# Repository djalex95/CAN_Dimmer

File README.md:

# CAN LED Dimmer

Vierkanaliger LED-Dimmer mit CAN-Bus und Bluetooth LE, entwickelt in KiCad 10.

## Eckdaten

- 4 LED-KanÃ¤le mit je etwa 5 A, PWM 1 kHz (strombegrenzte LED-Streifen als Last angenommen)
- Versorgung 12 V nominal, 24 V optional; zwei Eingangszweige mit je 10-A-Sicherung und TVS-Schutz
- Steuerung: STM32G0B1CEU6 (UFQFPN48, 7 x 7 mm, 512 KB Flash) mit externem 8-MHz-Quarz
- Kommunikation: CAN (TLT9251VLE, externe Terminierung) und Bluetooth LE (WÃ¼rth Proteus-IV 2621011024000)
- High-Side-Schalter BTS70202 (je zwei KanÃ¤le) mit Stromdiagnose, P-Kanal-MOSFETs fÃ¼r die Lastzweige
- Spannungsversorgung: LM5166X (5 V) und NCP730 (3,3 V)
- 4 TastereingÃ¤nge (J5), EEPROM M24C04, Programmierung Ã¼ber Tag-Connect TC2030 (J1, J2)
- Platine 100 Ã— 75 mm, 4 Lagen, 1,6 mm, nur Oberseite bestÃ¼ckt, vier Montagebohrungen Ã˜ 3,2 mm

## Aufbau des Projekts

| Datei / Ordner | Inhalt |
|---|---|
| `CAN LED Dimmer.kicad_pro` | Projektdatei, hier Ã¶ffnen |
| `CAN LED Dimmer.kicad_sch` | Schaltplan-Ãœbersicht (hierarchisch) |
| `CAN_LED_Dimmer_MCU.kicad_sch` | Blatt MCU, Bluetooth, CAN |
| `CAN_LED_Dimmer_2.kicad_sch` | Blatt Spannungsversorgung |
| `CAN_LED_Dimmer_3.kicad_sch` | Blatt LED-AusgÃ¤nge |
| `CAN LED Dimmer.kicad_pcb` | Platinenlayout |
| `CAN LED Dimmer-eagle-import.kicad_sym` | Symbolbibliothek (aus Eagle/Fusion importiert) |
| `CAN_LED_Dimmer-layout.pretty` | angepasste Footprint-Varianten fÃ¼r dieses Layout |
| `3dmodels/` | 3D-Modelle, Herkunft siehe `3dmodels/README-3D.md` |

Alle Bibliotheken und 3D-Modelle liegen im Projekt und sind Ã¼ber `${KIPRJMOD}` eingebunden. Nach dem Klonen reicht eine KiCad-10-Installation, es mÃ¼ssen keine Bibliothekspfade angepasst werden.

## Ã–ffnen

1. Repository klonen oder als ZIP herunterladen.
2. In KiCad 10 die Datei `CAN LED Dimmer.kicad_pro` Ã¶ffnen.

## Stand

Arbeitsstand, noch keine Fertigungsfreigabe:

- Layout vollstÃ¤ndig geroutet, DRC zuletzt ohne Fehler und offene Verbindungen; bekannte Bibliotheks- und Silkscreen-Warnungen sind noch offen.
- ERC hat noch offene Meldungen, vor allem durch importierte Pin-Typen.
- Strombelastbarkeit, Thermik bei viermal 5 A und Schaltflanken sind am Prototyp zu prÃ¼fen.
- Lagenaufbau und Kupferdicke sind mit dem Hersteller festzulegen.
- Eingangsschutz fÃ¼r 24 V und Transienten ist bewusst zurÃ¼ckgestellt.

Historische Reviews, Zwischenstände und unbenutzte Importdateien wurden separat außerhalb des Projektordners archiviert. Die aktive Footprint-Bibliothek ist `CAN_LED_Dimmer-layout.pretty`.

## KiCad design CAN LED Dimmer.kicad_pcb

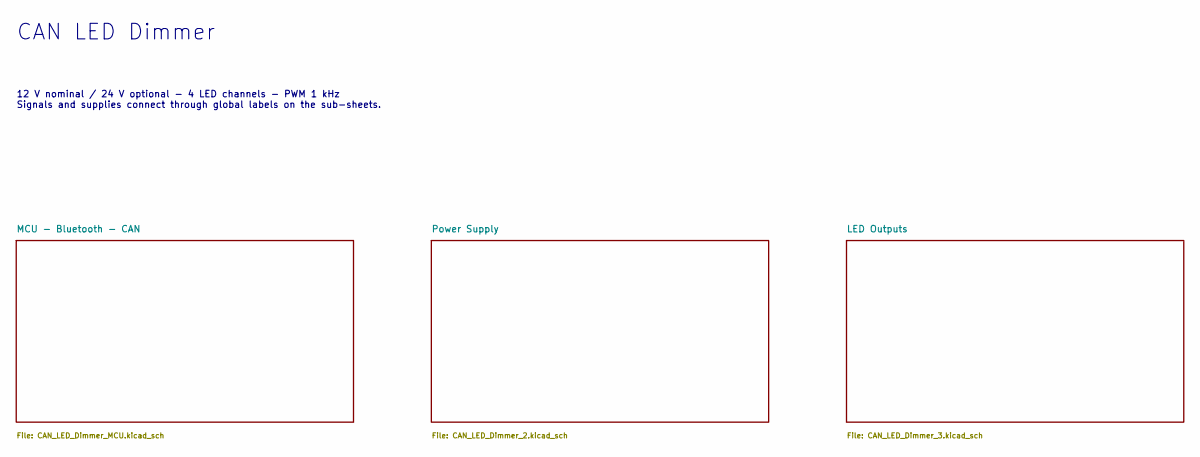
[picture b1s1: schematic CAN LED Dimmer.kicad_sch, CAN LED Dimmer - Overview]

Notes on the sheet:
CAN LED Dimmer
12 V nominal / 24 V optional - 4 LED channels - PWM 1 kHz Signals and supplies connect through global labels on the sub-sheets.

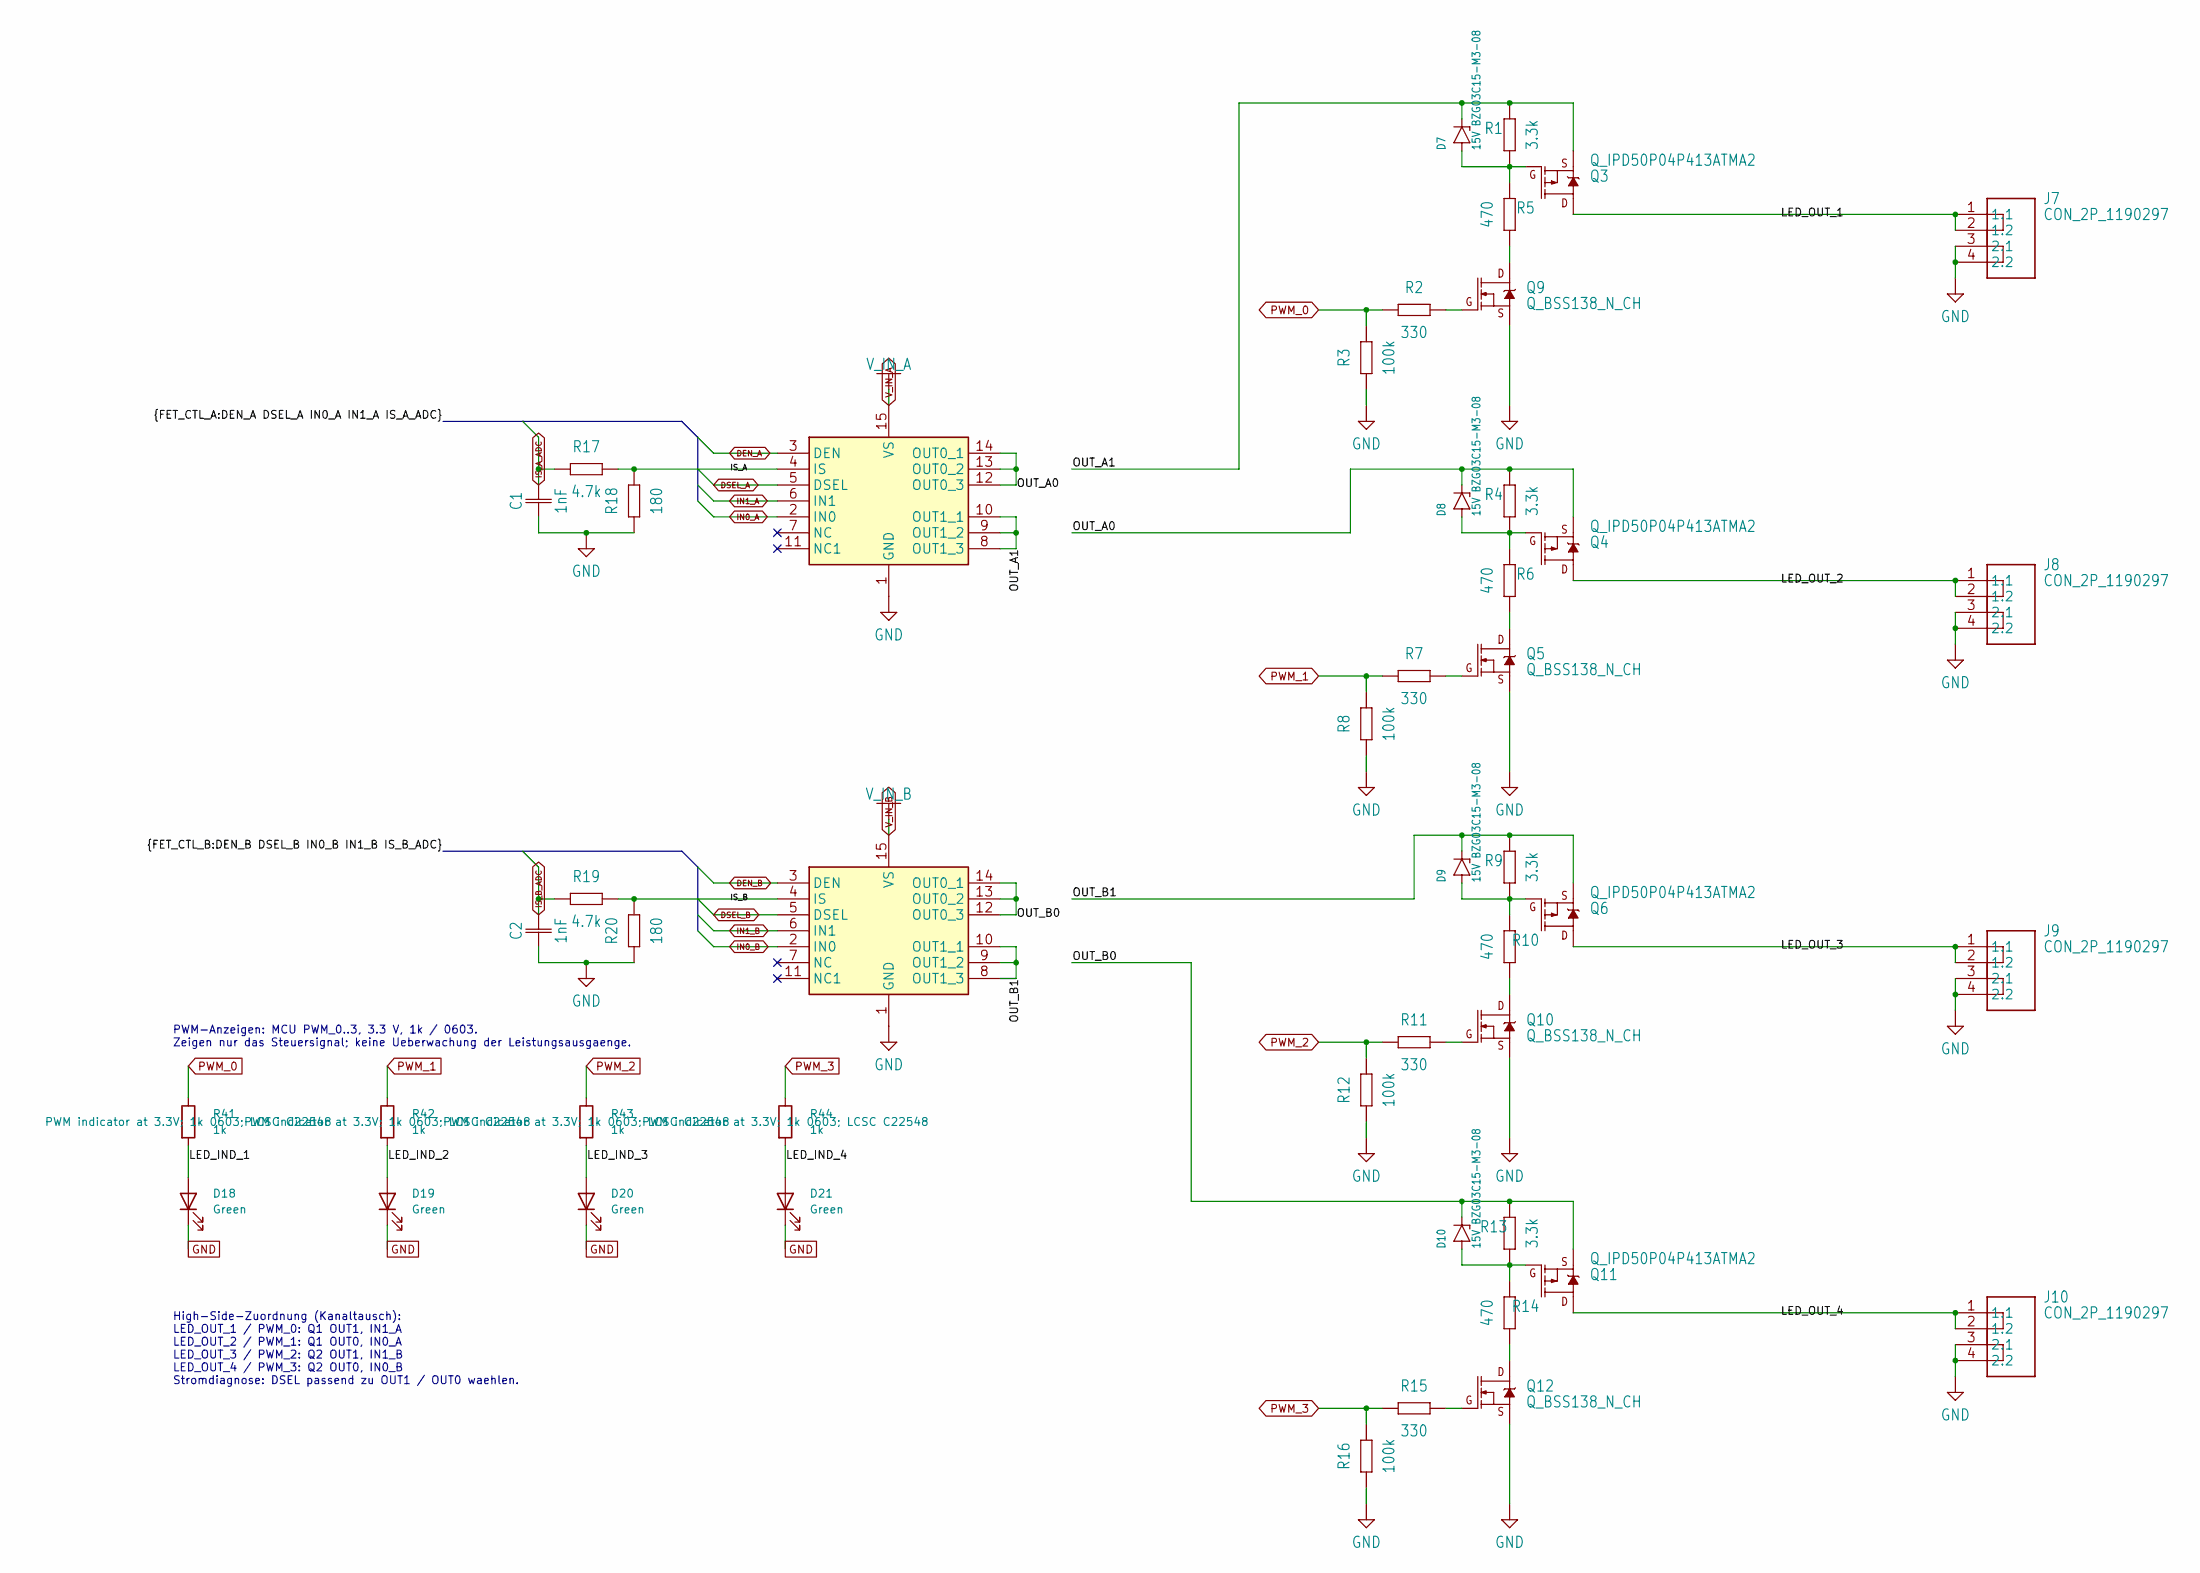
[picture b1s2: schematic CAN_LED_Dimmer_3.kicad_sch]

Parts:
C1: 1nF; CAPC1608X85_C1
C2: 1nF; CAPC1608X85_C2
D7: 15V BZG03C15-M3-08; D_SMA_AC_D7; MPN BZG03C15-M3-08
D8: 15V BZG03C15-M3-08; D_SMA_AC_D8; MPN BZG03C15-M3-08
D9: 15V BZG03C15-M3-08; D_SMA_AC_D9; MPN BZG03C15-M3-08
D10: 15V BZG03C15-M3-08; D_SMA_AC_D10; MPN BZG03C15-M3-08
D18: Green; LED_0603_1608Metric_D18; MPN KP-1608SGC
D19: Green; LED_0603_1608Metric_D19; MPN KP-1608SGC
D20: Green; LED_0603_1608Metric_D20; MPN KP-1608SGC
D21: Green; LED_0603_1608Metric_D21; MPN KP-1608SGC
J7: CON_2P_1190297; 1190297_J7; MPN 1190297
J8: CON_2P_1190297; 1190297_J8; MPN 1190297
J9: CON_2P_1190297; 1190297_J9; MPN 1190297
J10: CON_2P_1190297; 1190297_J10; MPN 1190297
Q1: PWR_BTS70202EPAXUMA1; SOP65P600X114-15T265X400N_Q1; MPN BTS70202EPAXUMA1
Q2: PWR_BTS70202EPAXUMA1; SOP65P600X114-15T265X400N_Q2; MPN BTS70202EPAXUMA1
Q3: Q_IPD50P04P413ATMA2; PG-TO252-3-313_Q3; MPN IPD50P04P413ATMA2
Q4: Q_IPD50P04P413ATMA2; PG-TO252-3-313_Q4; MPN IPD50P04P413ATMA2
Q5: Q_BSS138_N_CH; SOT95P237X110-3N_Q5; MPN BSS138
Q6: Q_IPD50P04P413ATMA2; PG-TO252-3-313_Q6; MPN IPD50P04P413ATMA2
Q9: Q_BSS138_N_CH; SOT95P237X110-3N_Q9; MPN BSS138
Q10: Q_BSS138_N_CH; SOT95P237X110-3N_Q10; MPN BSS138
Q11: Q_IPD50P04P413ATMA2; PG-TO252-3-313_Q11; MPN IPD50P04P413ATMA2
Q12: Q_BSS138_N_CH; SOT95P237X110-3N_Q12; MPN BSS138
R1: 3.3k; RESC3216X70_R1
R2: 330; RESC2012X65_R2
R3: 100k; RESC1608X60_R3
R4: 3.3k; RESC3216X70_R4
R5: 470; R_1206_3216Metric_R5
R6: 470; R_1206_3216Metric_R6
R7: 330; RESC2012X65_R7
R8: 100k; RESC1608X60_R8
R9: 3.3k; RESC3216X70_R9
R10: 470; R_1206_3216Metric_R10
R11: 330; RESC2012X65_R11
R12: 100k; RESC1608X60_R12
R13: 3.3k; RESC3216X70_R13
R14: 470; R_1206_3216Metric_R14
R15: 330; RESC2012X65_R15
R16: 100k; RESC1608X60_R16
R17: 4.7k; RESC1608X60_R17
R18: 180; RESC1608X60_R18
R19: 4.7k; RESC1608X60_R19
R20: 180; RESC1608X60_R20
R41: 1k; RESC1608X60_R41; Tolerance 1%; MPN RC0603FR-071KL
R42: 1k; RESC1608X60_R42; Tolerance 1%; MPN RC0603FR-071KL
R43: 1k; RESC1608X60_R43; Tolerance 1%; MPN RC0603FR-071KL
R44: 1k; RESC1608X60_R44; Tolerance 1%; MPN RC0603FR-071KL

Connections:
/LED Outputs/IS_A: Q1.4 (IS), R17.2, R18.2
/LED Outputs/IS_B: Q2.4 (IS), R19.2, R20.2
/LED Outputs/LED_IND_1: D18.2 (A), R41.2
/LED Outputs/LED_IND_2: D19.2 (A), R42.2
/LED Outputs/LED_IND_3: D20.2 (A), R43.2
/LED Outputs/LED_IND_4: D21.2 (A), R44.2
/LED Outputs/LED_OUT_1: J7.1 (1.1), J7.2 (1.2), Q3.3 (D)
/LED Outputs/LED_OUT_2: J8.1 (1.1), J8.2 (1.2), Q4.3 (D)
/LED Outputs/LED_OUT_3: J9.1 (1.1), J9.2 (1.2), Q6.3 (D)
/LED Outputs/LED_OUT_4: J10.1 (1.1), J10.2 (1.2), Q11.3 (D)
/LED Outputs/OUT_A0: D8.C (K), Q1.12 (OUT0_3), Q1.13 (OUT0_2), Q1.14 (OUT0_1), Q4.2 (S), R4.2
/LED Outputs/OUT_A1: D7.C (K), Q1.8 (OUT1_3), Q1.9 (OUT1_2), Q1.10 (OUT1_1), Q3.2 (S), R1.2
/LED Outputs/OUT_B0: D10.C (K), Q2.12 (OUT0_3), Q2.13 (OUT0_2), Q2.14 (OUT0_1), Q11.2 (S), R13.2
/LED Outputs/OUT_B1: D9.C (K), Q2.8 (OUT1_3), Q2.9 (OUT1_2), Q2.10 (OUT1_1), Q6.2 (S), R9.2
DEN_A: Q1.3 (DEN); also elsewhere on the board
DEN_B: Q2.3 (DEN); also elsewhere on the board
DSEL_A: Q1.5 (DSEL); also elsewhere on the board
DSEL_B: Q2.5 (DSEL); also elsewhere on the board
GND: C1.1, C2.1, D18.1 (K), D19.1 (K), D20.1 (K), D21.1 (K), J7.3 (2.1), J7.4 (2.2), J8.3 (2.1), J8.4 (2.2), J9.3 (2.1), J9.4 (2.2), J10.3 (2.1), J10.4 (2.2), Q1.1 (GND), Q2.1 (GND), Q5.2 (S), Q9.2 (S), Q10.2 (S), Q12.2 (S), R3.1, R8.1, R12.1, R16.1, R18.1, R20.1; also elsewhere on the board
IN0_A: Q1.2 (IN0); also elsewhere on the board
IN0_B: Q2.2 (IN0); also elsewhere on the board
IN1_A: Q1.6 (IN1); also elsewhere on the board
IN1_B: Q2.6 (IN1); also elsewhere on the board
IS_A_ADC: C1.2, R17.1; also elsewhere on the board
IS_B_ADC: C2.2, R19.1; also elsewhere on the board
unnamed: D7.A, Q3.1 (G), R1.1, R5.1
unnamed: D8.A, Q4.1 (G), R4.1, R6.1
unnamed: Q5.3 (D), R6.2
unnamed: Q5.1 (G), R7.2
unnamed: D9.A, Q6.1 (G), R9.1, R10.1
unnamed: Q9.3 (D), R5.2
unnamed: Q9.1 (G), R2.2
unnamed: Q10.3 (D), R10.2
unnamed: Q10.1 (G), R11.2
unnamed: D10.A, Q11.1 (G), R13.1, R14.1
unnamed: Q12.3 (D), R14.2
unnamed: Q12.1 (G), R15.2
PWM_0: R2.1, R3.2, R41.1; also elsewhere on the board
PWM_1: R7.1, R8.2, R42.1; also elsewhere on the board
PWM_2: R11.1, R12.2, R43.1; also elsewhere on the board
PWM_3: R15.1, R16.2, R44.1; also elsewhere on the board
V_IN_A: Q1.15 (VS); also elsewhere on the board
V_IN_B: Q2.15 (VS); also elsewhere on the board

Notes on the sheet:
High-Side-Zuordnung (Kanaltausch): LED_OUT_1 / PWM_0: Q1 OUT1, IN1_A LED_OUT_2 / PWM_1: Q1 OUT0, IN0_A LED_OUT_3 / PWM_2: Q2 OUT1, IN1_B LED_OUT_4 / PWM_3: Q2 OUT0, IN0_B Stromdiagnose: DSEL passend zu OUT1 / OUT0 waehlen.
PWM-Anzeigen: MCU PWM_0..3, 3.3 V, 1k / 0603. Zeigen nur das Steuersignal; keine Ueberwachung der Leistungsausgaenge.

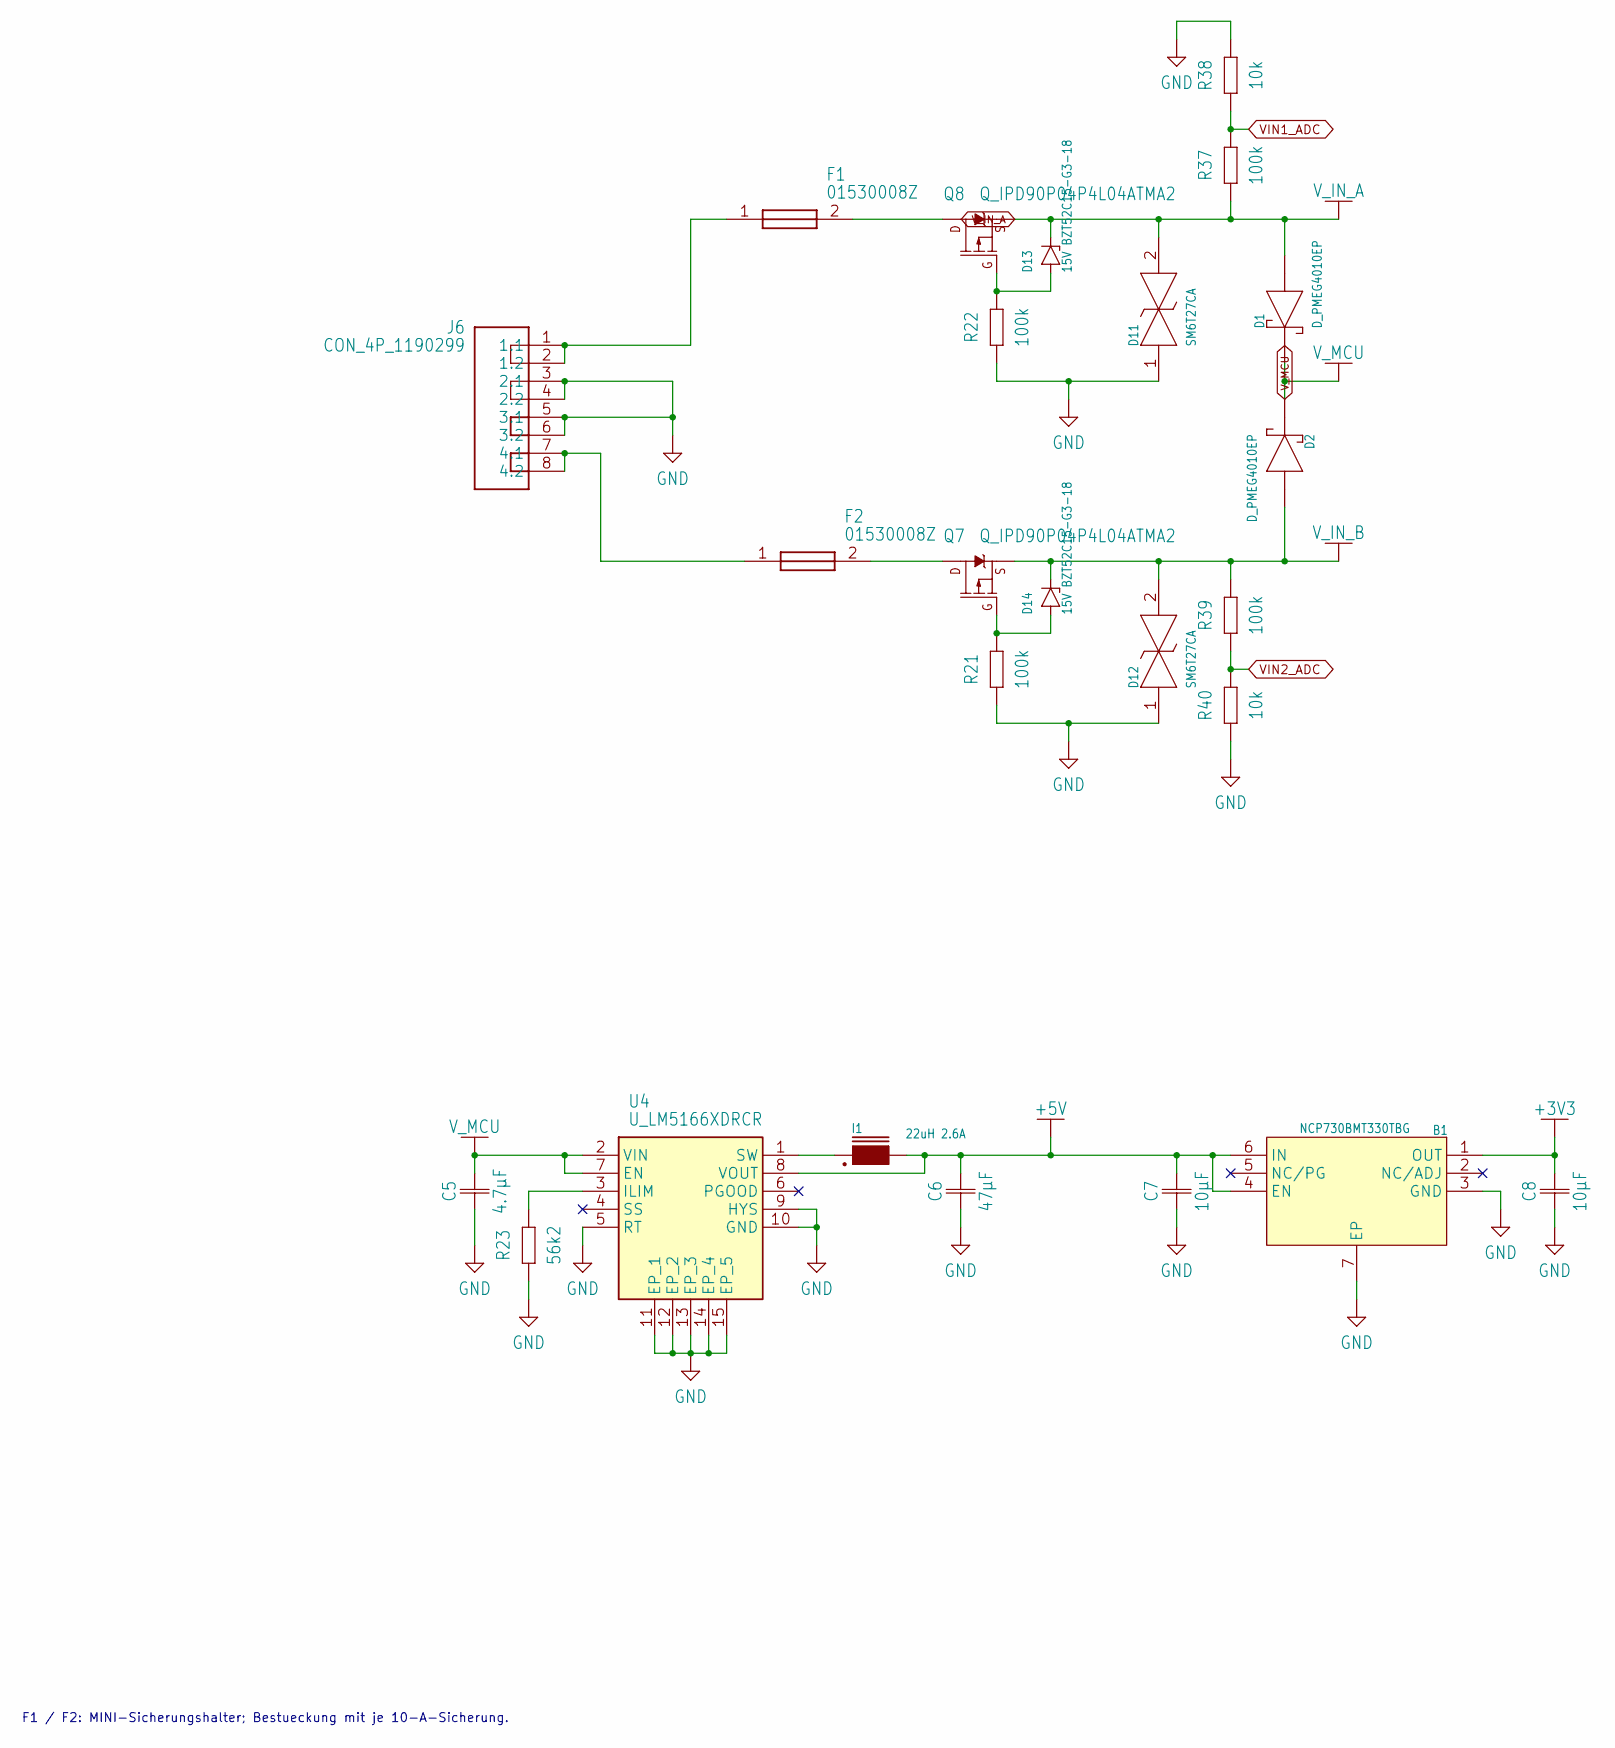
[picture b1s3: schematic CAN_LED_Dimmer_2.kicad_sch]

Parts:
B1: NCP730BMT330TBG; SON65P200X200X80-7N_B1; MANUFACTURER_PART_NUMBER NCP730BMT330TBG; MOUSER_PART_NUMBER 863-NCP730BMT330TBG
C5: 4.7µF; CAPC3216X135_C5
C6: 47µF; CAPC3216X135_C6
C7: 10µF; CAPC1608X85_C7
C8: 10µF; CAPC1608X85_C8
D1: D_PMEG4010EP; SODFL4725X110N_SOD128_D1; MPN PMEG4010EP
D2: D_PMEG4010EP; SODFL4725X110N_SOD128_D2; MPN PMEG4010EP
D11: SM6T27CA; DIONM5436X265N_D11; MANUFACTURER_PART_NUMBER SM6T27CA; MOUSER_PART_NUMBER 511-SM6T27CA
D12: SM6T27CA; DIONM5436X265N_D12; MANUFACTURER_PART_NUMBER SM6T27CA; MOUSER_PART_NUMBER 511-SM6T27CA
D13: 15V BZT52C15-G3-18; D_SOD-123_AC_D13; MPN BZT52C15-G3-18
D14: 15V BZT52C15-G3-18; D_SOD-123_AC_D14; MPN BZT52C15-G3-18
F1: 01530008Z; 01530008_F1; MANUFACTURER_PART_NUMBER 01530008Z; MOUSER_PART_NUMBER 576-01530008Z
F2: 01530008Z; 01530008_F2; MANUFACTURER_PART_NUMBER 01530008Z; MOUSER_PART_NUMBER 576-01530008Z
I1: 22uH 2.6A; SMMS0630-220M_I1; MPN SMMS0630-220M
J6: CON_4P_1190299; 1190299_J6; MPN 1190299
Q7: Q_IPD90P04P4L04ATMA2; PG-TO252-3-313_Q7; MPN IPD90P04P4L04ATMA2
Q8: Q_IPD90P04P4L04ATMA2; PG-TO252-3-313_Q8; MPN IPD90P04P4L04ATMA2
R21: 100k; RESC1608X60_R21
R22: 100k; RESC1608X60_R22
R23: 56k2; RESC1608X60_R23
R37: 100k; RESC1608X60_R37
R38: 10k; RESC1608X60_R38
R39: 100k; RESC1608X60_R39
R40: 10k; RESC1608X60_R40
U4: U_LM5166XDRCR; VSON-10-EP_U4; MPN LM5166XDRCR

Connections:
+3V3: B1.1 (OUT), C8.2; also elsewhere on the board
+5V: B1.4 (EN), B1.6 (IN), C6.2, C7.2, I1.2, U4.8 (VOUT); also elsewhere on the board
GND: B1.3 (GND), B1.7 (EP), C5.1, C6.1, C7.1, C8.1, D11.1, D12.1, J6.3 (2.1), J6.4 (2.2), J6.5 (3.1), J6.6 (3.2), R21.1, R22.1, R23.1, R38.2, R40.1, U4.5 (RT), U4.9 (HYS), U4.10 (GND), U4.11 (EP_1), U4.12 (EP_2), U4.13 (EP_3), U4.14 (EP_4), U4.15 (EP_5); also elsewhere on the board
unnamed: F1.1, J6.1 (1.1), J6.2 (1.2)
unnamed: F2.1, J6.7 (4.1), J6.8 (4.2)
unnamed: F2.2, Q7.3 (D)
unnamed: D14.A, Q7.1 (G), R21.2
unnamed: F1.2, Q8.3 (D)
unnamed: D13.A, Q8.1 (G), R22.2
unnamed: R23.2, U4.3 (ILIM)
unnamed: I1.1, U4.1 (SW)
VIN1_ADC: R37.2, R38.1; also elsewhere on the board
VIN2_ADC: R39.1, R40.2; also elsewhere on the board
V_IN_A: D1.A, D11.2, D13.C (K), Q8.2 (S), R37.1; also elsewhere on the board
V_IN_B: D2.A, D12.2, D14.C (K), Q7.2 (S), R39.2; also elsewhere on the board
V_MCU: C5.2, D1.C (K), D2.C (K), U4.2 (VIN), U4.7 (EN)

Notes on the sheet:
F1 / F2: MINI-Sicherungshalter; Bestueckung mit je 10-A-Sicherung.

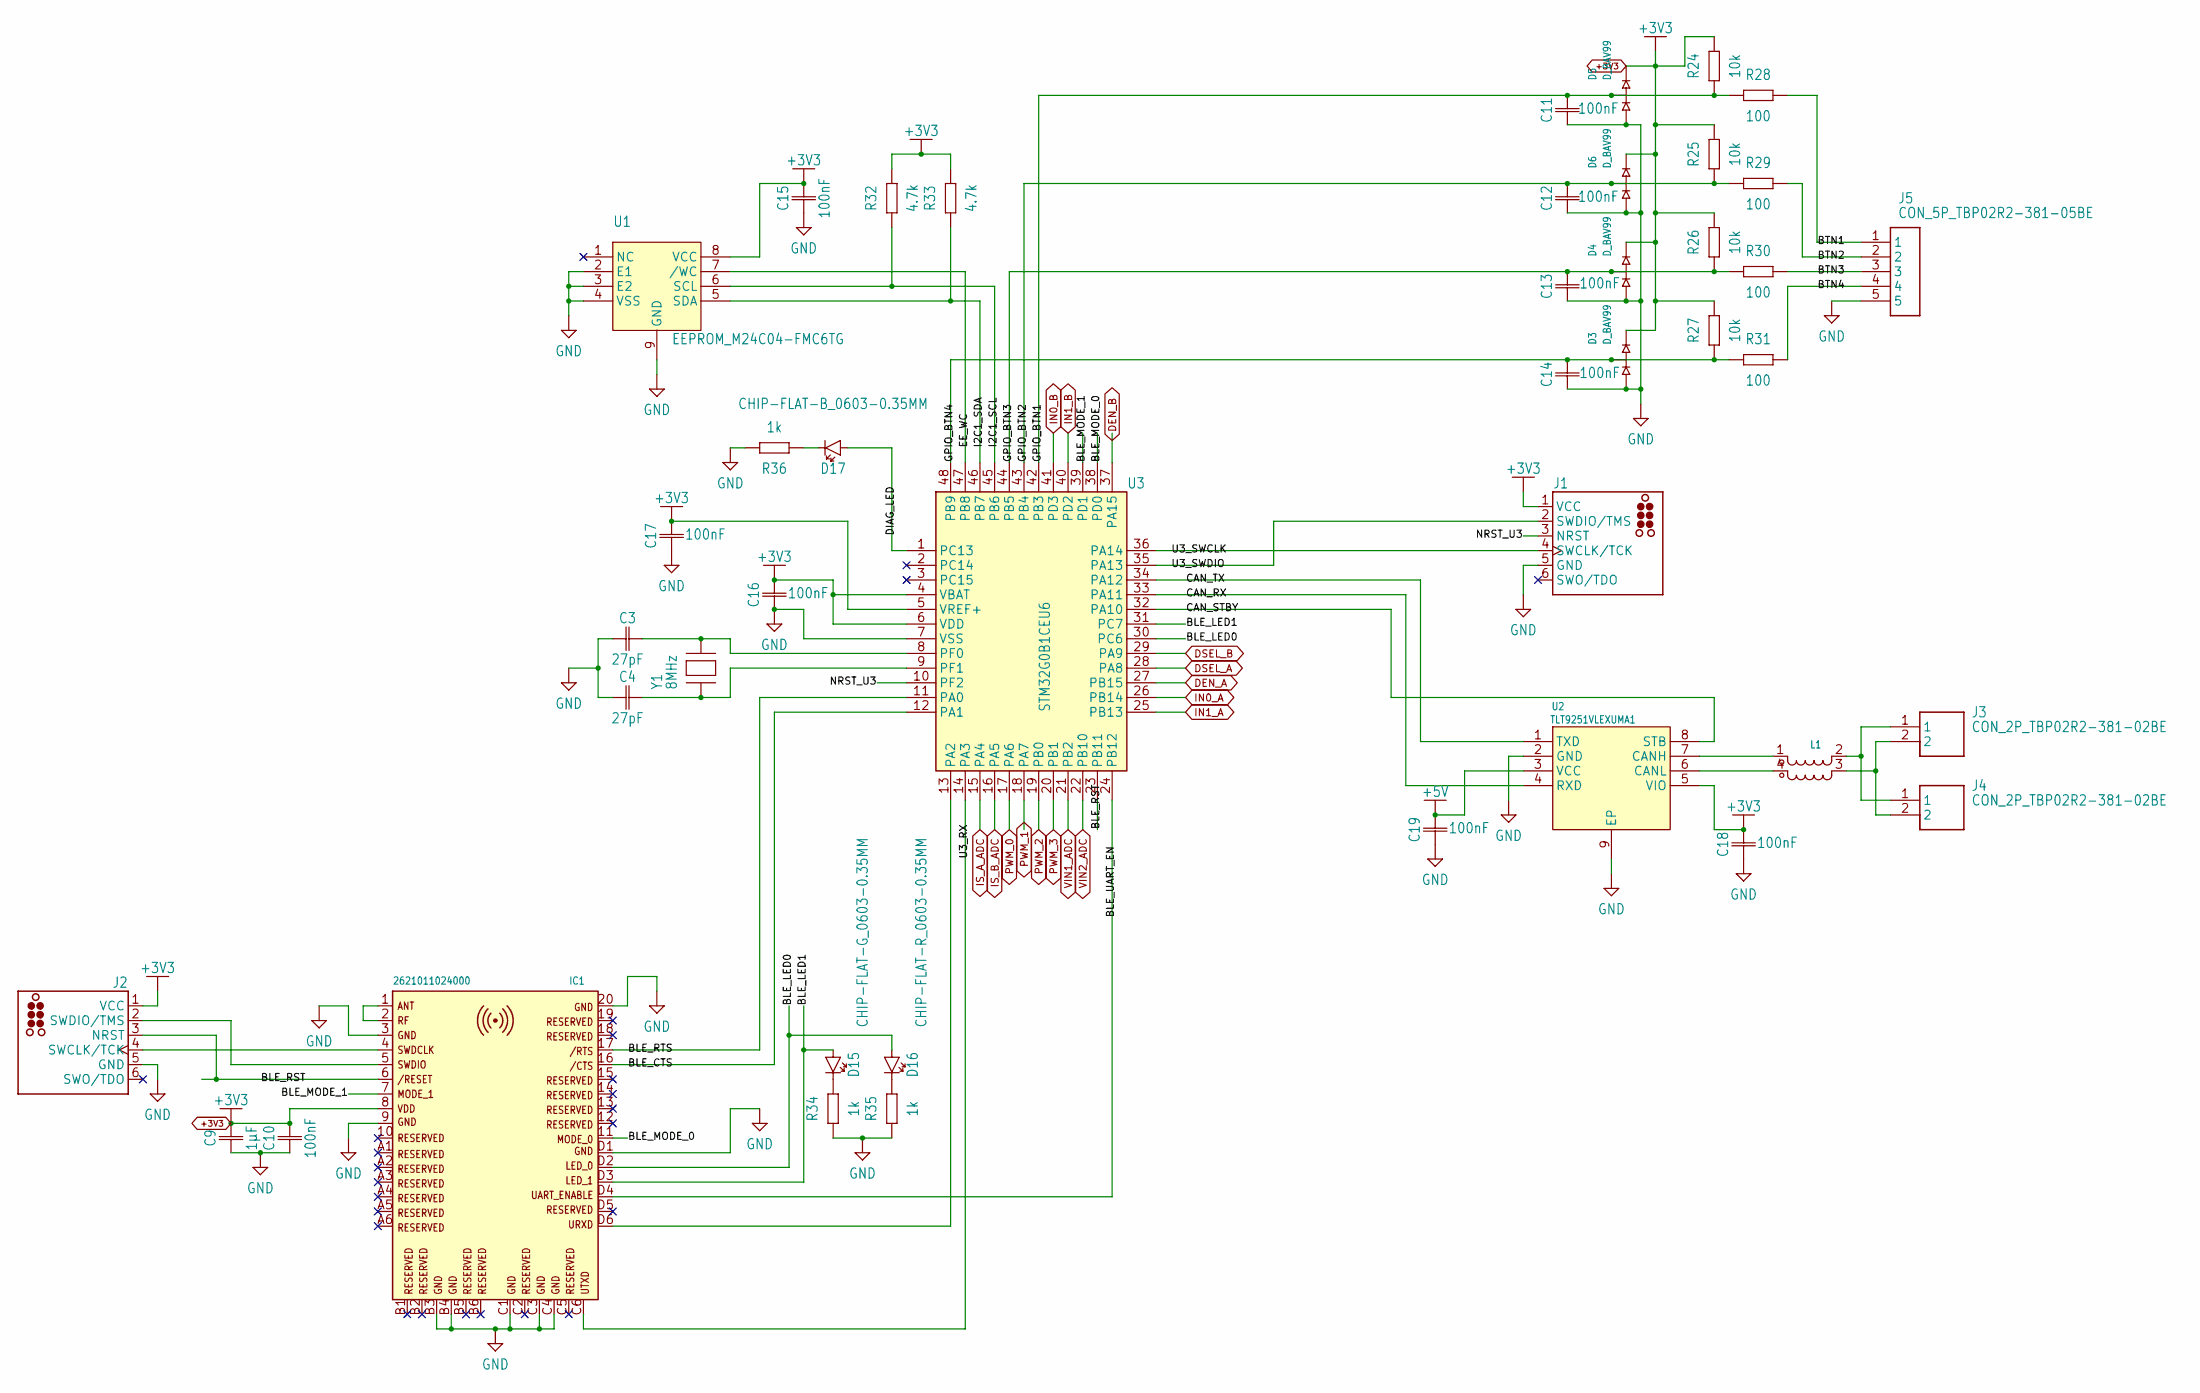
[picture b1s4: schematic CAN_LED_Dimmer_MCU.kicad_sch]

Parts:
C3: 27pF; CAPC1608X85_C3; MPN CL10C270JB8NNNC
C4: 27pF; CAPC1608X85_C4; MPN CL10C270JB8NNNC
C9: 1µF; CAPC1608X85_C9
C10: 100nF; CAPC1608X85_C10
C11: 100nF; CAPC1608X85_C11
C12: 100nF; CAPC1608X85_C12
C13: 100nF; CAPC1608X85_C13
C14: 100nF; CAPC1608X85_C14
C15: 100nF; CAPC1608X85_C15
C16: 100nF; CAPC1608X85_C16
C17: 100nF; CAPC1608X85_C17
C18: 100nF; CAPC1608X85_C18
C19: 100nF; CAPC1608X85_C19
D3: D_BAV99; SOT95P237X110-3N_D3; MPN BAV99
D4: D_BAV99; SOT95P237X110-3N_D4; MPN BAV99
D5: D_BAV99; SOT95P237X110-3N_D5; MPN BAV99
D6: D_BAV99; SOT95P237X110-3N_D6; MPN BAV99
D15: CHIP-FLAT-G_0603-0.35MM; LEDC1608X35N_FLAT-G_D15
D16: CHIP-FLAT-R_0603-0.35MM; LEDC1608X35N_FLAT-R_D16
D17: CHIP-FLAT-B_0603-0.35MM; LEDC1608X35N_FLAT-B_D17
IC1: 2621011024000; WIRL-BTLE_2621011024000_IC1; PART-NUMBER 2621011024000
J1: CON_TC2030_SWD; TC2030_J1
J2: CON_TC2030_SWD; TC2030_J2
J3: CON_2P_TBP02R2-381-02BE; TBP02R2-381-02BE_J3; MPN TBP02R2-381-02BE
J4: CON_2P_TBP02R2-381-02BE; TBP02R2-381-02BE_J4; MPN TBP02R2-381-02BE
J5: CON_5P_TBP02R2-381-05BE; TBP02R2-381-05BE_J5; MPN TBP02R2-381-05BE
L1: *; FIL_SRF0504-302Y_L1
R24: 10k; RESC1608X60_R24
R25: 10k; RESC1608X60_R25
R26: 10k; RESC1608X60_R26
R27: 10k; RESC1608X60_R27
R28: 100; RESC1608X60_R28
R29: 100; RESC1608X60_R29
R30: 100; RESC1608X60_R30
R31: 100; RESC1608X60_R31
R32: 4.7k; RESC1608X60_R32
R33: 4.7k; RESC1608X60_R33
R34: 1k; RESC1608X60_R34
R35: 1k; RESC1608X60_R35
R36: 1k; RESC1608X60_R36
U1: EEPROM_M24C04-FMC6TG; SON50P300X200X60-9T139N_U1
U2: TLT9251VLEXUMA1; SON65P300X300X110-9N_U2
U3: STM32G0B1CEU6; QFN-48-1EP_7x7mm_P0.5mm_EP5.6x5.6mm_U3; MPN STM32G0B1CEU6
Y1: 8MHz; OSCCC720X520X130N_7X5X1.3_Y1; MPN 0175M4-8.000F18DTNJL

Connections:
+3V3: C9.2, C10.2, C15.2, C16.2, C17.2, C18.2, D3.2 (K), D4.2 (K), D5.2 (K), D6.2 (K), IC1.8, J1.1 (VCC), J2.1 (VCC), R24.2, R25.2, R26.2, R27.2, R32.2, R33.2, U1.8 (VCC), U2.5 (VIO), U3.4 (VBAT), U3.5 (VREF+), U3.6 (VDD); also elsewhere on the board
+5V: C19.2, U2.3 (VCC); also elsewhere on the board
/MCU - Bluetooth - CAN/BLE_CTS: IC1.16, U3.12 (PA1)
/MCU - Bluetooth - CAN/BLE_LED0: D16.A, IC1.D2, U3.30 (PC6)
/MCU - Bluetooth - CAN/BLE_LED1: D15.A, IC1.D3, U3.31 (PC7)
/MCU - Bluetooth - CAN/BLE_MODE_0: IC1.11, U3.38 (PD0)
/MCU - Bluetooth - CAN/BLE_MODE_1: IC1.7, U3.39 (PD1)
/MCU - Bluetooth - CAN/BLE_RST: IC1.6, J2.3 (NRST), U3.23 (PB11)
/MCU - Bluetooth - CAN/BLE_RTS: IC1.17, U3.11 (PA0)
/MCU - Bluetooth - CAN/BLE_UART_EN: IC1.D4, U3.24 (PB12)
/MCU - Bluetooth - CAN/BTN1: J5.1, R28.2
/MCU - Bluetooth - CAN/BTN2: J5.2, R29.2
/MCU - Bluetooth - CAN/BTN3: J5.3, R30.2
/MCU - Bluetooth - CAN/BTN4: J5.4, R31.2
/MCU - Bluetooth - CAN/CAN_RX: U2.4 (RXD), U3.33 (PA11)
/MCU - Bluetooth - CAN/CAN_STBY: U2.8 (STB), U3.32 (PA10)
/MCU - Bluetooth - CAN/CAN_TX: U2.1 (TXD), U3.34 (PA12)
/MCU - Bluetooth - CAN/DIAG_LED: D17.A, U3.1 (PC13)
/MCU - Bluetooth - CAN/EE_WC: U1.7 (/WC), U3.47 (PB8)
/MCU - Bluetooth - CAN/GPIO_BTN1: C11.2, D5.3 (COMMON), R24.1, R28.1, U3.42 (PB3)
/MCU - Bluetooth - CAN/GPIO_BTN2: C12.2, D6.3 (COMMON), R25.1, R29.1, U3.43 (PB4)
/MCU - Bluetooth - CAN/GPIO_BTN3: C13.2, D4.3 (COMMON), R26.1, R30.1, U3.44 (PB5)
/MCU - Bluetooth - CAN/GPIO_BTN4: C14.2, D3.3 (COMMON), R27.1, R31.1, U3.48 (PB9)
/MCU - Bluetooth - CAN/I2C1_SCL: R32.1, U1.6 (SCL), U3.45 (PB6)
/MCU - Bluetooth - CAN/I2C1_SDA: R33.1, U1.5 (SDA), U3.46 (PB7)
/MCU - Bluetooth - CAN/NRST_U3: J1.3 (NRST), U3.10 (PF2)
/MCU - Bluetooth - CAN/U3_RX: IC1.C6, U3.14 (PA3)
/MCU - Bluetooth - CAN/U3_SWCLK: J1.4 (SWCLK/TCK), U3.36 (PA14)
/MCU - Bluetooth - CAN/U3_SWDIO: J1.2 (SWDIO/TMS), U3.35 (PA13)
DEN_A: U3.27 (PB15); also elsewhere on the board
DEN_B: U3.37 (PA15); also elsewhere on the board
DSEL_A: U3.28 (PA8); also elsewhere on the board
DSEL_B: U3.29 (PA9); also elsewhere on the board
GND: C3.1, C4.1, C9.1, C10.1, C11.1, C12.1, C13.1, C14.1, C15.1, C16.1, C17.1, C18.1, C19.1, D3.1 (A), D4.1 (A), D5.1 (A), D6.1 (A), IC1.3, IC1.9, IC1.20, IC1.B3, IC1.B4, IC1.C1, IC1.C3, IC1.C4, IC1.D1, J1.5 (GND), J2.5 (GND), J5.5, R34.1, R35.1, R36.2, U1.2 (E1), U1.3 (E2), U1.4 (VSS), U1.9 (GND), U2.2 (GND), U2.9 (EP), U3.7 (VSS), U3.49 (VSS); also elsewhere on the board
IN0_A: U3.26 (PB14); also elsewhere on the board
IN0_B: U3.41 (PD3); also elsewhere on the board
IN1_A: U3.25 (PB13); also elsewhere on the board
IN1_B: U3.40 (PD2); also elsewhere on the board
IS_A_ADC: U3.15 (PA4); also elsewhere on the board
IS_B_ADC: U3.16 (PA5); also elsewhere on the board
unnamed: D15.C, R34.2
unnamed: D16.C, R35.2
unnamed: D17.C, R36.1
unnamed: IC1.1, IC1.2
unnamed: IC1.4, J2.4 (SWCLK/TCK)
unnamed: IC1.5, J2.2 (SWDIO/TMS)
unnamed: J3.1, J4.1, L1.2
unnamed: J3.2, J4.2, L1.3
unnamed: L1.1, U2.7 (CANH)
unnamed: L1.4, U2.6 (CANL)
unnamed: IC1.D6, U3.13 (PA2)
unnamed: C3.2, U3.8 (PF0), Y1.3
unnamed: C4.2, U3.9 (PF1), Y1.1
PWM_0: U3.17 (PA6); also elsewhere on the board
PWM_1: U3.18 (PA7); also elsewhere on the board
PWM_2: U3.19 (PB0); also elsewhere on the board
PWM_3: U3.20 (PB1); also elsewhere on the board
VIN1_ADC: U3.21 (PB2); also elsewhere on the board
VIN2_ADC: U3.22 (PB10); also elsewhere on the board

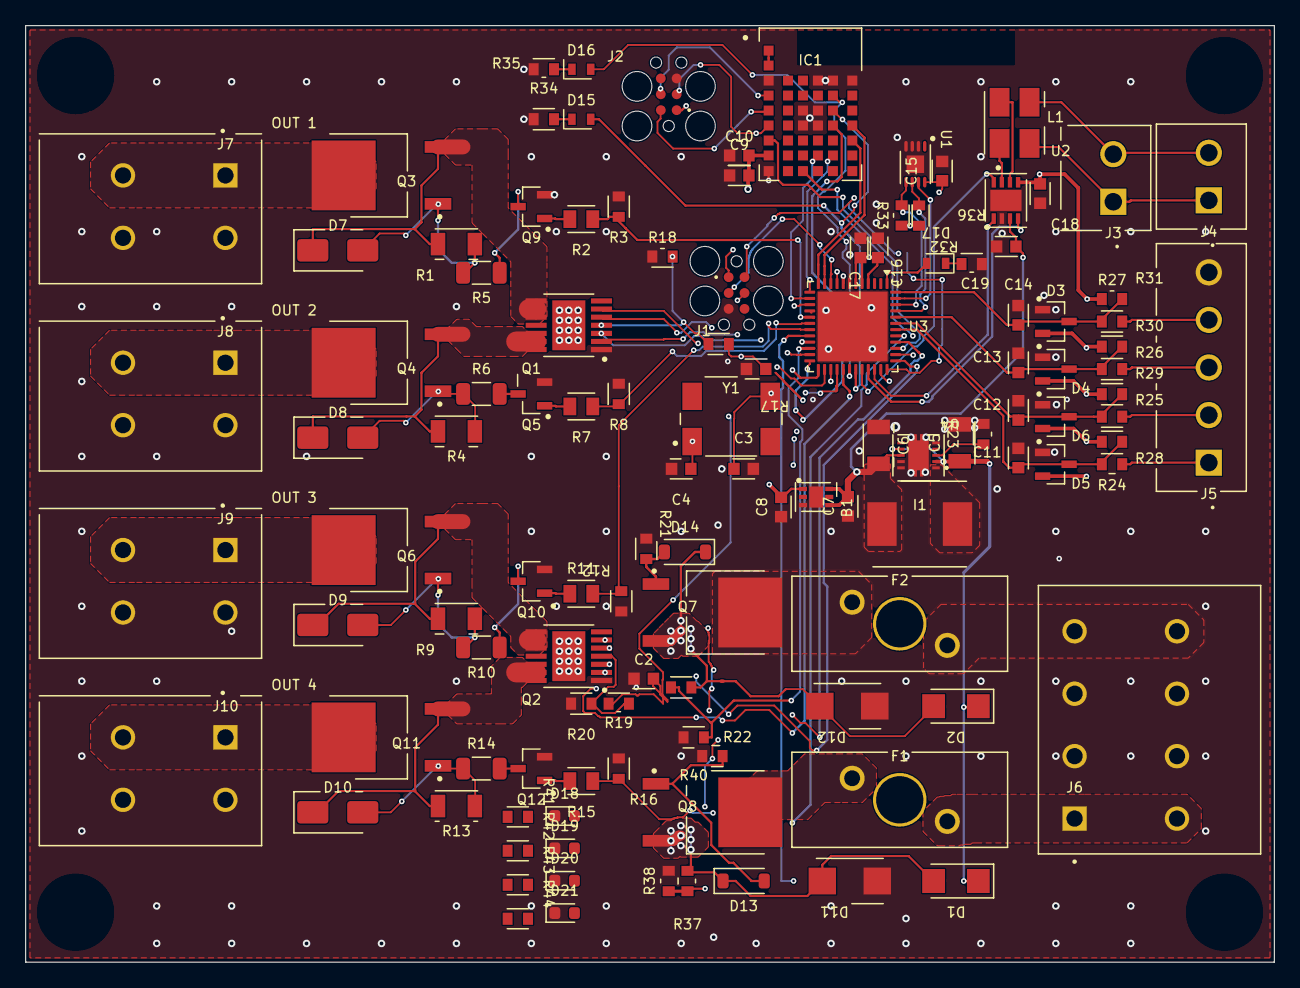
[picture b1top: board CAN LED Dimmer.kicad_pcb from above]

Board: 4 copper layers, 100.0 x 75.0 mm, 117 parts (0 on the bottom side), 96 nets.
